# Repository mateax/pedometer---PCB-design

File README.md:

# pedometer-PCB-design

PCB design and electrical schematic for step counter by EAGLE software

### Circuit

Components required: 
* Attiny85 IC
* MPU6050
* OLED Display Module
* 2× Push Buttons
* 5× 10KΩ Resistors (SMD)

### How it works?
This Arduino based step counter is powered by a 3V coin cell, making it easy to carry when you go out for a walk or jog.
The program in this project uses the MPU6050 to measure the magnitude of the acceleration along the 3 axis (X, Y, and Z). Then it calculates the difference of the acceleration magnitude between the previous and current values. If the difference is greater than a certain threshold (For walking greater than 6 and for running greater than 10), then it increases the step count accordingly. The total steps taken are then displayed on OLED Display.

### Circuit diagram
The schematic for the MPU6050 Step Counter is given below:

The above image shows the circuit diagram for interfacing MPU6050 and OLED Display with Attiny85 IC. The interface between MPU6050, OLED Display, and Arduino must be implemented using I2C Protocol. Hence, the SCLPin (PB2) of the ATtiny85 is connected to the SCLPin of the MPU6050 and OLED Display respectively. Similarly, the SDAPin (PB0) of the ATtiny85 is connected to the SDAPin of the MPU6050 and OLED Display. Two pushbuttons are also connected to the PB3 & PB4 pin of ATtiny85 IC. These buttons can be used to scroll the text or change the text on display.

### 
### PCB - top layer

#### 
### PCB - bottom layer

####  
### 3D PCB view

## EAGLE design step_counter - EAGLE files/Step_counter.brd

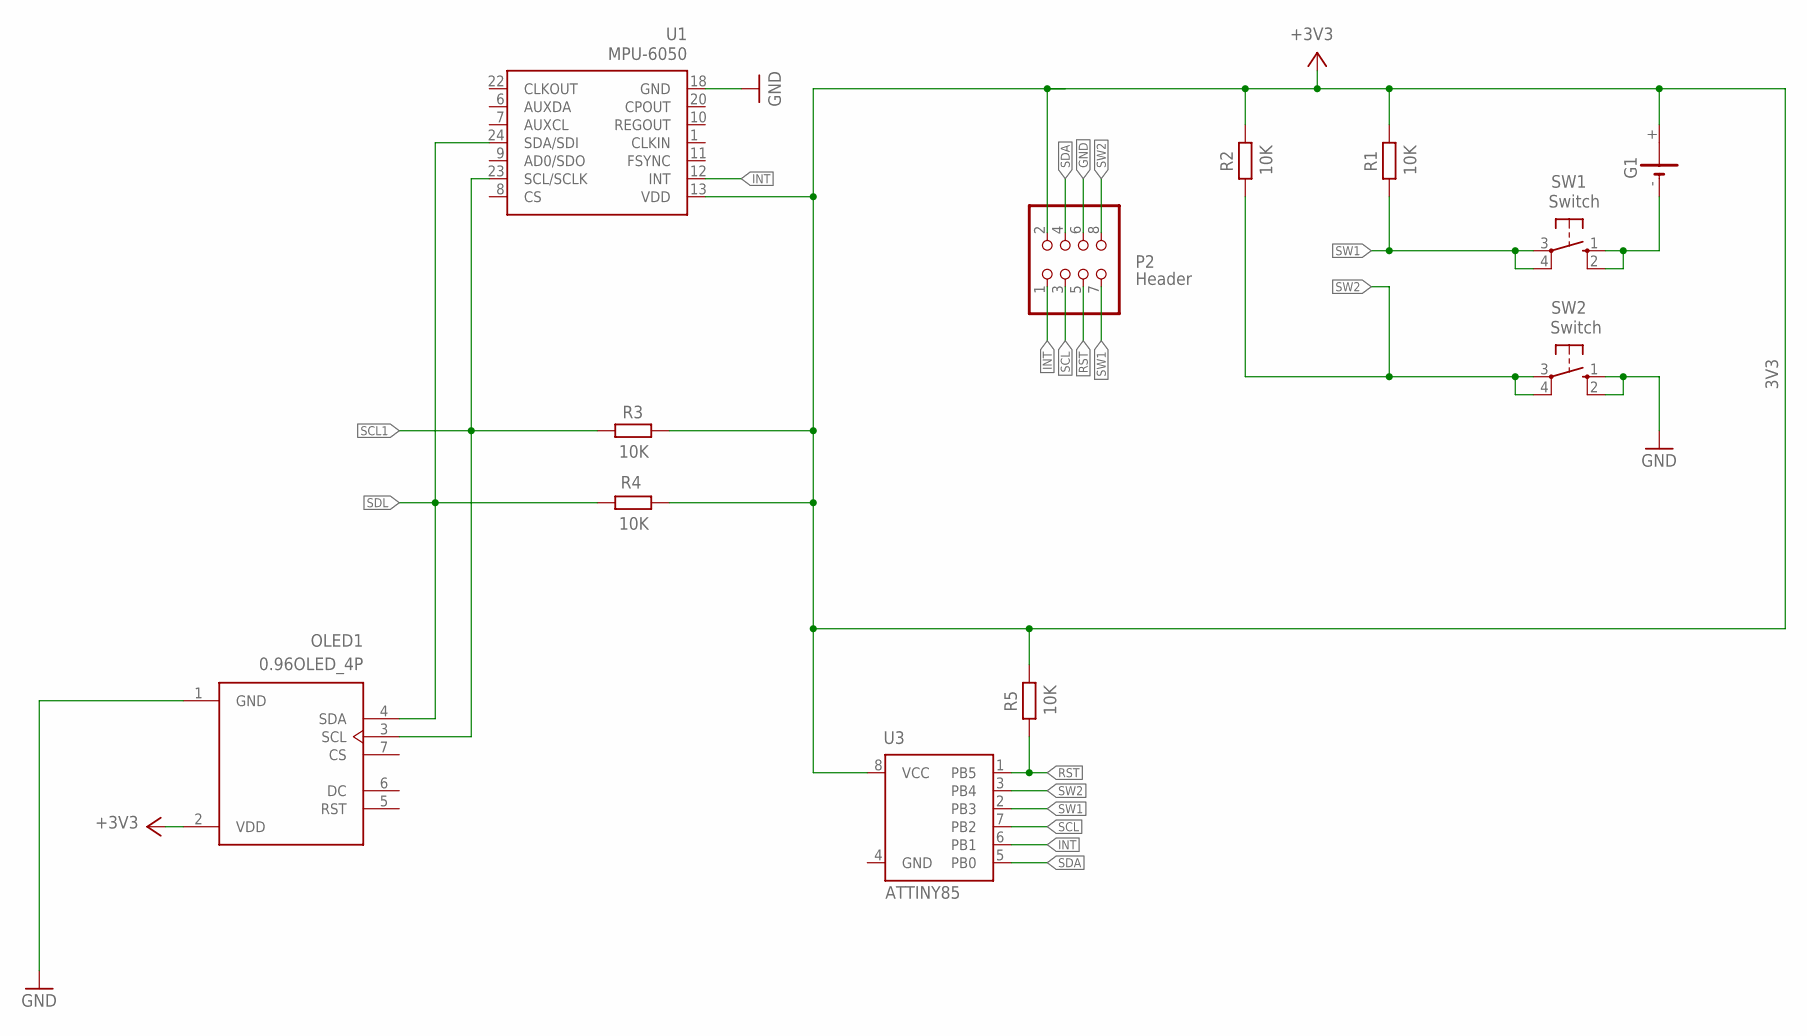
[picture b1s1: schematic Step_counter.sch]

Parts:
G1: 3V3; CR2032V
OLED1: 0.96OLED_4P; LCD_AOM12864A0-1.54WW-ANO
P2: Header; 2X04
R1, R2, R3, R4, R5: 10K; 0204/7
SW1, SW2: Switch; B3F-10XX
U1: MPU-6050; QFN-24-EP
U3: ATTINY85

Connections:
+3V3: G1.+, OLED1.2 (VDD), P2.2, R1.2, R2.2, R3.2, R4.2, R5.2, U1.13 (VDD), U3.8 (VCC)
GND: G1.-, OLED1.1 (GND), P2.6, SW1.1 (S), SW1.2 (S1), SW2.1 (S), SW2.2 (S1), U1.18 (GND)
INT: P2.1, U1.12 (INT), U3.6 (PB1)
RST: P2.5, R5.1, U3.1 (PB5)
SCL: P2.3, U3.7 (PB2)
SCL1: OLED1.3 (SCL), R3.1, U1.23 (SCL/SCLK)
SDA: P2.4, U3.5 (PB0)
SDL: OLED1.4 (SDA), R4.1, U1.24 (SDA/SDI)
SW1: P2.7, R1.1, SW1.3, SW1.4 (P1), U3.2 (PB3)
SW2: P2.8, R2.1, SW2.3, SW2.4 (P1), U3.3 (PB4)

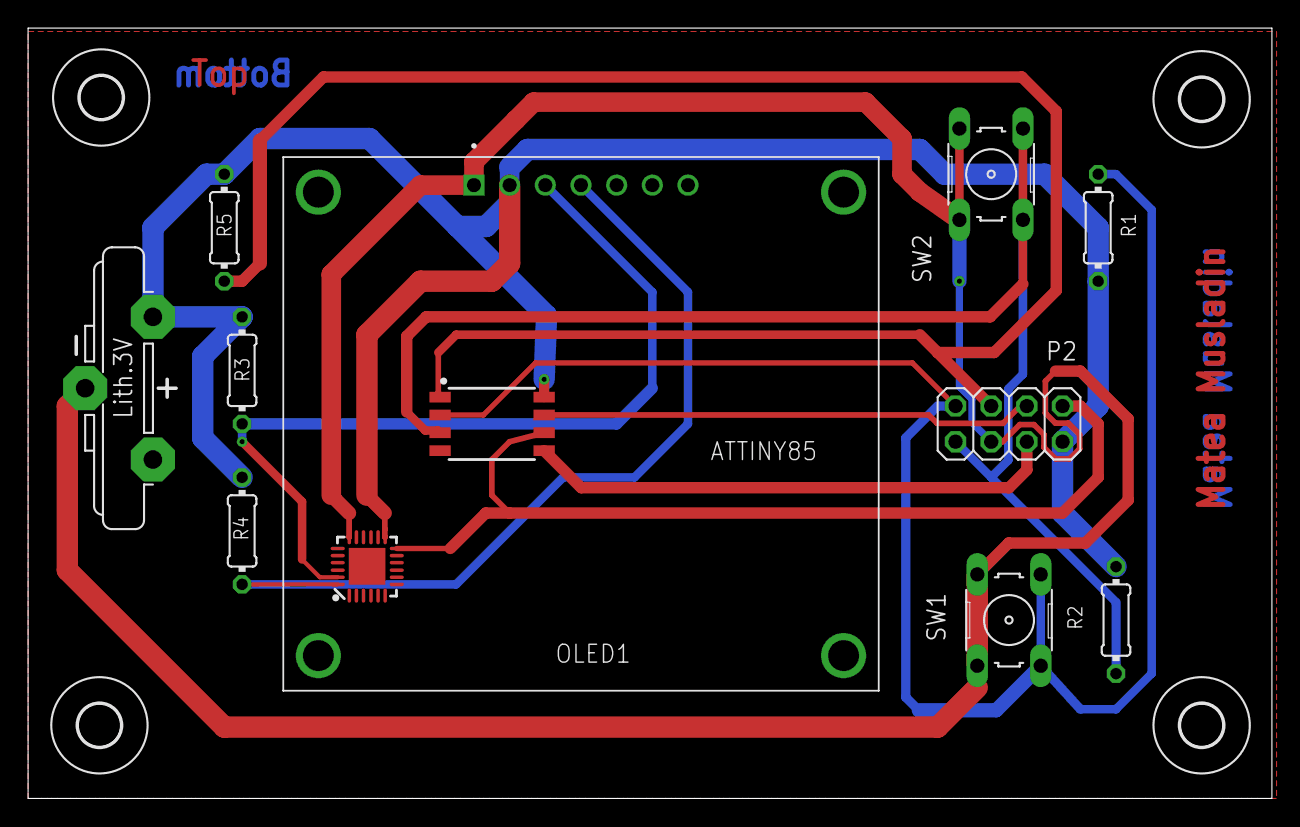
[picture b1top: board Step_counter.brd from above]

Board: 2 copper layers, 88.6 x 54.9 mm, 16 parts (0 on the bottom side), 10 nets.

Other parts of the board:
U$1, U$2, U$3, U$4: 3,0

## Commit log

2022-11-24 added files
2022-11-24 Updated READ.md

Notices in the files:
parts and their libraries:
SparkFun-Sensors: Licensing: Creative Commons ShareAlike 4.0 International - https://creativecommons.org/licenses/by-sa/4.0
